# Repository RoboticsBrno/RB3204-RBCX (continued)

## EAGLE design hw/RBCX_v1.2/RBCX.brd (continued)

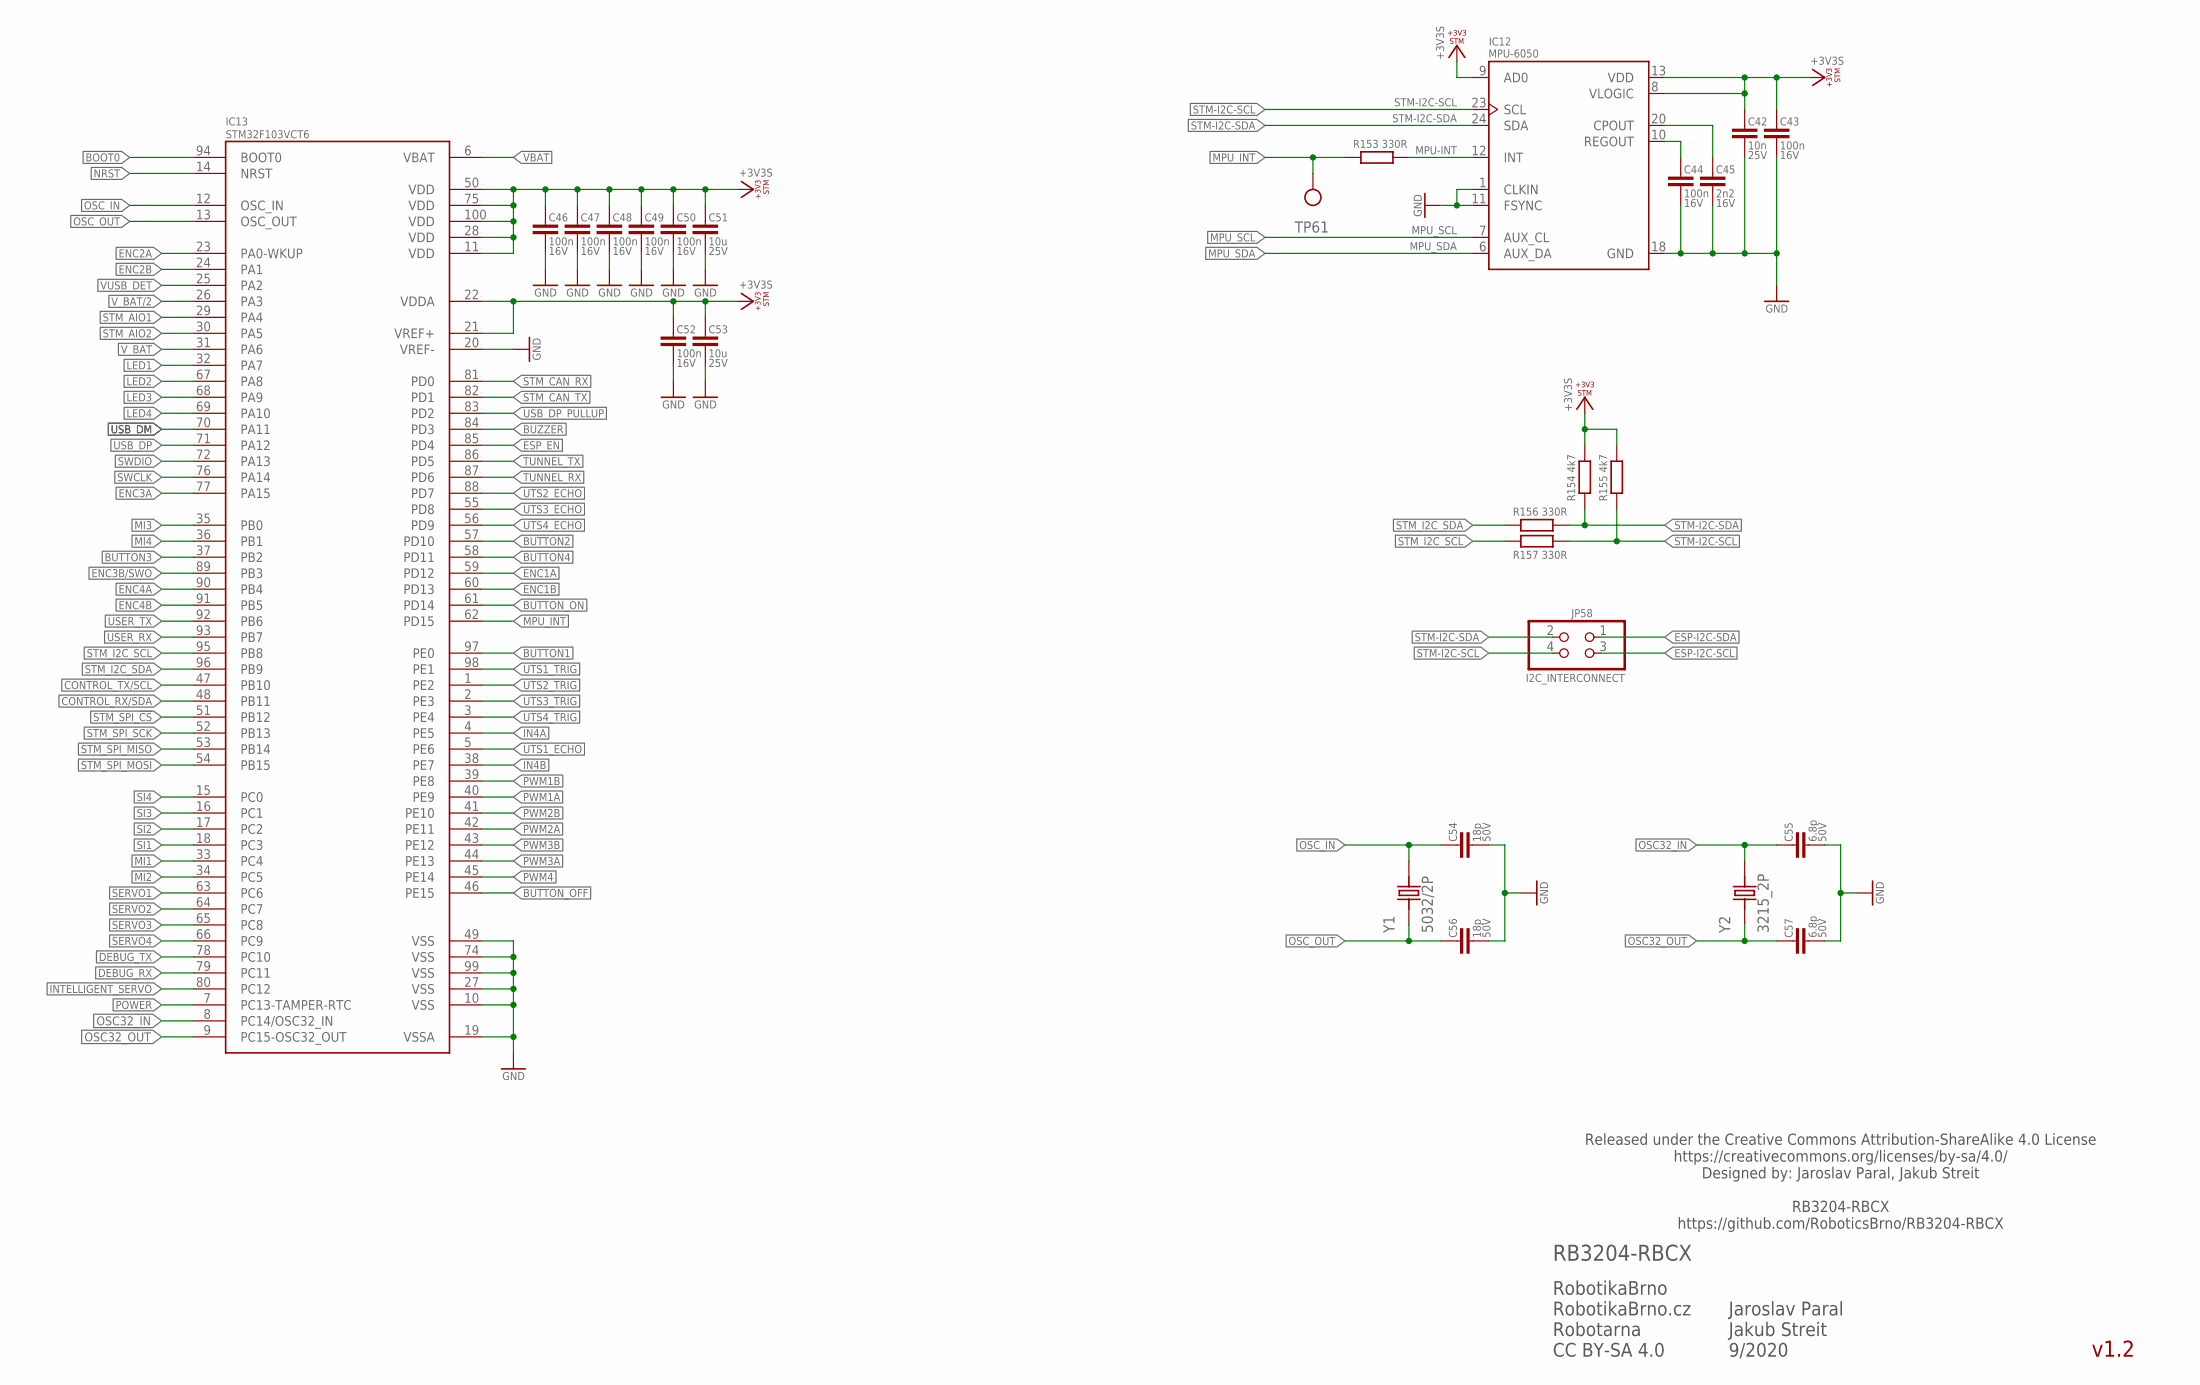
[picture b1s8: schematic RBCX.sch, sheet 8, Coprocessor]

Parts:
C42: 10n; C0402; VOLTAGE 25V
C43, C44, C46, C47, C48, C49, C50, C52: 100n; C0402; VOLTAGE 16V
C45: 2n2; C0402; VOLTAGE 16V
C51, C53: 10u; C0805; VOLTAGE 25V
C54, C56: 18p; C0402; VOLTAGE 50V
C55, C57: 6.8p; C0402; VOLTAGE 50V
IC12: MPU-6050; QFN50P400X400X95-24N
IC13: STM32F103VCT6; QFP50P1600X1600X160-100N_STM32F103VCT6
JP58: I2C_INTERCONNECT; 2X02
R153, R156, R157: 330R; R0402
R154, R155: 4k7; R0402
TP61: TP_06MM; TP_06
Y1: 5032/2P; OSCCC500X320X135
Y2: 3215_2P; SMD-3215_2P

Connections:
+3V3S: C42.1, C43.2, C46.2, C47.2, C48.2, C49.2, C50.2, C51.2, C52.2, C53.2, IC12.8 (VLOGIC), IC12.9 (AD0), IC12.13 (VDD), IC13.11 (VDD), IC13.21 (VREF+), IC13.22 (VDDA), IC13.28 (VDD), IC13.50 (VDD), IC13.75 (VDD), IC13.100 (VDD), R154.2, R155.2; also elsewhere on the board
BOOT0: IC13.94 (BOOT0); also elsewhere on the board
BUTTON1: IC13.97 (PE0); also elsewhere on the board
BUTTON2: IC13.57 (PD10); also elsewhere on the board
BUTTON3: IC13.37 (PB2); also elsewhere on the board
BUTTON4: IC13.58 (PD11); also elsewhere on the board
BUTTON_OFF: IC13.46 (PE15); also elsewhere on the board
BUTTON_ON: IC13.61 (PD14); also elsewhere on the board
BUZZER: IC13.84 (PD3); also elsewhere on the board
CONTROL_RX/SDA: IC13.48 (PB11); also elsewhere on the board
CONTROL_TX/SCL: IC13.47 (PB10); also elsewhere on the board
CPOUT: C45.2, IC12.20 (CPOUT)
DEBUG_RX: IC13.79 (PC11); also elsewhere on the board
DEBUG_TX: IC13.78 (PC10); also elsewhere on the board
ENC1A: IC13.59 (PD12); also elsewhere on the board
ENC1B: IC13.60 (PD13); also elsewhere on the board
ENC2A: IC13.23 (PA0-WKUP); also elsewhere on the board
ENC2B: IC13.24 (PA1); also elsewhere on the board
ENC3A: IC13.77 (PA15); also elsewhere on the board
ENC3B/SWO: IC13.89 (PB3); also elsewhere on the board
ENC4A: IC13.90 (PB4); also elsewhere on the board
ENC4B: IC13.91 (PB5); also elsewhere on the board
ESP-I2C-SCL: JP58.3; also elsewhere on the board
ESP-I2C-SDA: JP58.1; also elsewhere on the board
ESP_EN: IC13.85 (PD4); also elsewhere on the board
GND: C42.2, C43.1, C44.1, C45.1, C46.1, C47.1, C48.1, C49.1, C50.1, C51.1, C52.1, C53.1, C54.1, C55.1, C56.1, C57.1, IC12.1 (CLKIN), IC12.11 (FSYNC), IC12.18 (GND), IC13.10 (VSS), IC13.19 (VSSA), IC13.20 (VREF-), IC13.27 (VSS), IC13.49 (VSS), IC13.74 (VSS), IC13.99 (VSS); also elsewhere on the board
IN4A: IC13.4 (PE5); also elsewhere on the board
IN4B: IC13.38 (PE7); also elsewhere on the board
INTELLIGENT_SERVO: IC13.80 (PC12); also elsewhere on the board
LED1: IC13.32 (PA7); also elsewhere on the board
LED2: IC13.67 (PA8); also elsewhere on the board
LED3: IC13.68 (PA9); also elsewhere on the board
LED4: IC13.69 (PA10); also elsewhere on the board
MI1: IC13.33 (PC4); also elsewhere on the board
MI2: IC13.34 (PC5); also elsewhere on the board
MI3: IC13.35 (PB0); also elsewhere on the board
MI4: IC13.36 (PB1); also elsewhere on the board
MPU-INT: IC12.12 (INT), R153.2
MPU_INT: IC13.62 (PD15), R153.1, TP61.P$1
MPU_SCL: IC12.7 (AUX_CL); also elsewhere on the board
MPU_SDA: IC12.6 (AUX_DA); also elsewhere on the board
NRST: IC13.14 (NRST); also elsewhere on the board
OSC32_IN: C55.2, IC13.8 (PC14/OSC32_IN), Y2.2
OSC32_OUT: C57.2, IC13.9 (PC15-OSC32_OUT), Y2.1
OSC_IN: C54.2, IC13.12 (OSC_IN), Y1.2
OSC_OUT: C56.2, IC13.13 (OSC_OUT), Y1.1
POWER: IC13.7 (PC13-TAMPER-RTC); also elsewhere on the board
PWM1A: IC13.40 (PE9); also elsewhere on the board
PWM1B: IC13.39 (PE8); also elsewhere on the board
PWM2A: IC13.42 (PE11); also elsewhere on the board
PWM2B: IC13.41 (PE10); also elsewhere on the board
PWM3A: IC13.44 (PE13); also elsewhere on the board
PWM3B: IC13.43 (PE12); also elsewhere on the board
PWM4: IC13.45 (PE14); also elsewhere on the board
REGOUT: C44.2, IC12.10 (REGOUT)
SERVO1: IC13.63 (PC6); also elsewhere on the board
SERVO2: IC13.64 (PC7); also elsewhere on the board
SERVO3: IC13.65 (PC8); also elsewhere on the board
SERVO4: IC13.66 (PC9); also elsewhere on the board
SI1: IC13.18 (PC3); also elsewhere on the board
SI2: IC13.17 (PC2); also elsewhere on the board
SI3: IC13.16 (PC1); also elsewhere on the board
SI4: IC13.15 (PC0); also elsewhere on the board
STM-I2C-SCL: IC12.23 (SCL), JP58.4, R155.1, R157.2; also elsewhere on the board
STM-I2C-SDA: IC12.24 (SDA), JP58.2, R154.1, R156.2; also elsewhere on the board
STM_AIO1: IC13.29 (PA4); also elsewhere on the board
STM_AIO2: IC13.30 (PA5); also elsewhere on the board
STM_CAN_RX: IC13.81 (PD0); also elsewhere on the board
STM_CAN_TX: IC13.82 (PD1); also elsewhere on the board
STM_I2C_SCL: IC13.95 (PB8), R157.1
STM_I2C_SDA: IC13.96 (PB9), R156.1
STM_SPI_!CS: IC13.51 (PB12); also elsewhere on the board
STM_SPI_MISO: IC13.53 (PB14); also elsewhere on the board
STM_SPI_MOSI: IC13.54 (PB15); also elsewhere on the board
STM_SPI_SCK: IC13.52 (PB13); also elsewhere on the board
SWCLK: IC13.76 (PA14); also elsewhere on the board
SWDIO: IC13.72 (PA13); also elsewhere on the board
TUNNEL_RX: IC13.87 (PD6); also elsewhere on the board
TUNNEL_TX: IC13.86 (PD5); also elsewhere on the board
USB_DM: IC13.70 (PA11); also elsewhere on the board
USB_DP: IC13.71 (PA12); also elsewhere on the board
USB_DP_PULLUP: IC13.83 (PD2); also elsewhere on the board
USER_RX: IC13.93 (PB7); also elsewhere on the board
USER_TX: IC13.92 (PB6); also elsewhere on the board
UTS1_ECHO: IC13.5 (PE6); also elsewhere on the board
UTS1_TRIG: IC13.98 (PE1); also elsewhere on the board
UTS2_ECHO: IC13.88 (PD7); also elsewhere on the board
UTS2_TRIG: IC13.1 (PE2); also elsewhere on the board
UTS3_ECHO: IC13.55 (PD8); also elsewhere on the board
UTS3_TRIG: IC13.2 (PE3); also elsewhere on the board
UTS4_ECHO: IC13.56 (PD9); also elsewhere on the board
UTS4_TRIG: IC13.3 (PE4); also elsewhere on the board
VBAT: IC13.6 (VBAT); also elsewhere on the board
VUSB_DET: IC13.25 (PA2); also elsewhere on the board
V_BAT: IC13.31 (PA6); also elsewhere on the board
V_BAT/2: IC13.26 (PA3); also elsewhere on the board

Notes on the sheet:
v1.2
RobotikaBrno RobotikaBrno.cz Robotarna CC BY-SA 4.0
RB3204-RBCX
Released under the Creative Commons Attribution-ShareAlike 4.0 License https://creativecommons.org/licenses/by-sa/4.0/ Designed by: Jaroslav Paral, Jakub Streit RB3204-RBCX https://github.com/RoboticsBrno/RB3204-RBCX
Jaroslav Paral Jakub Streit 9/2020

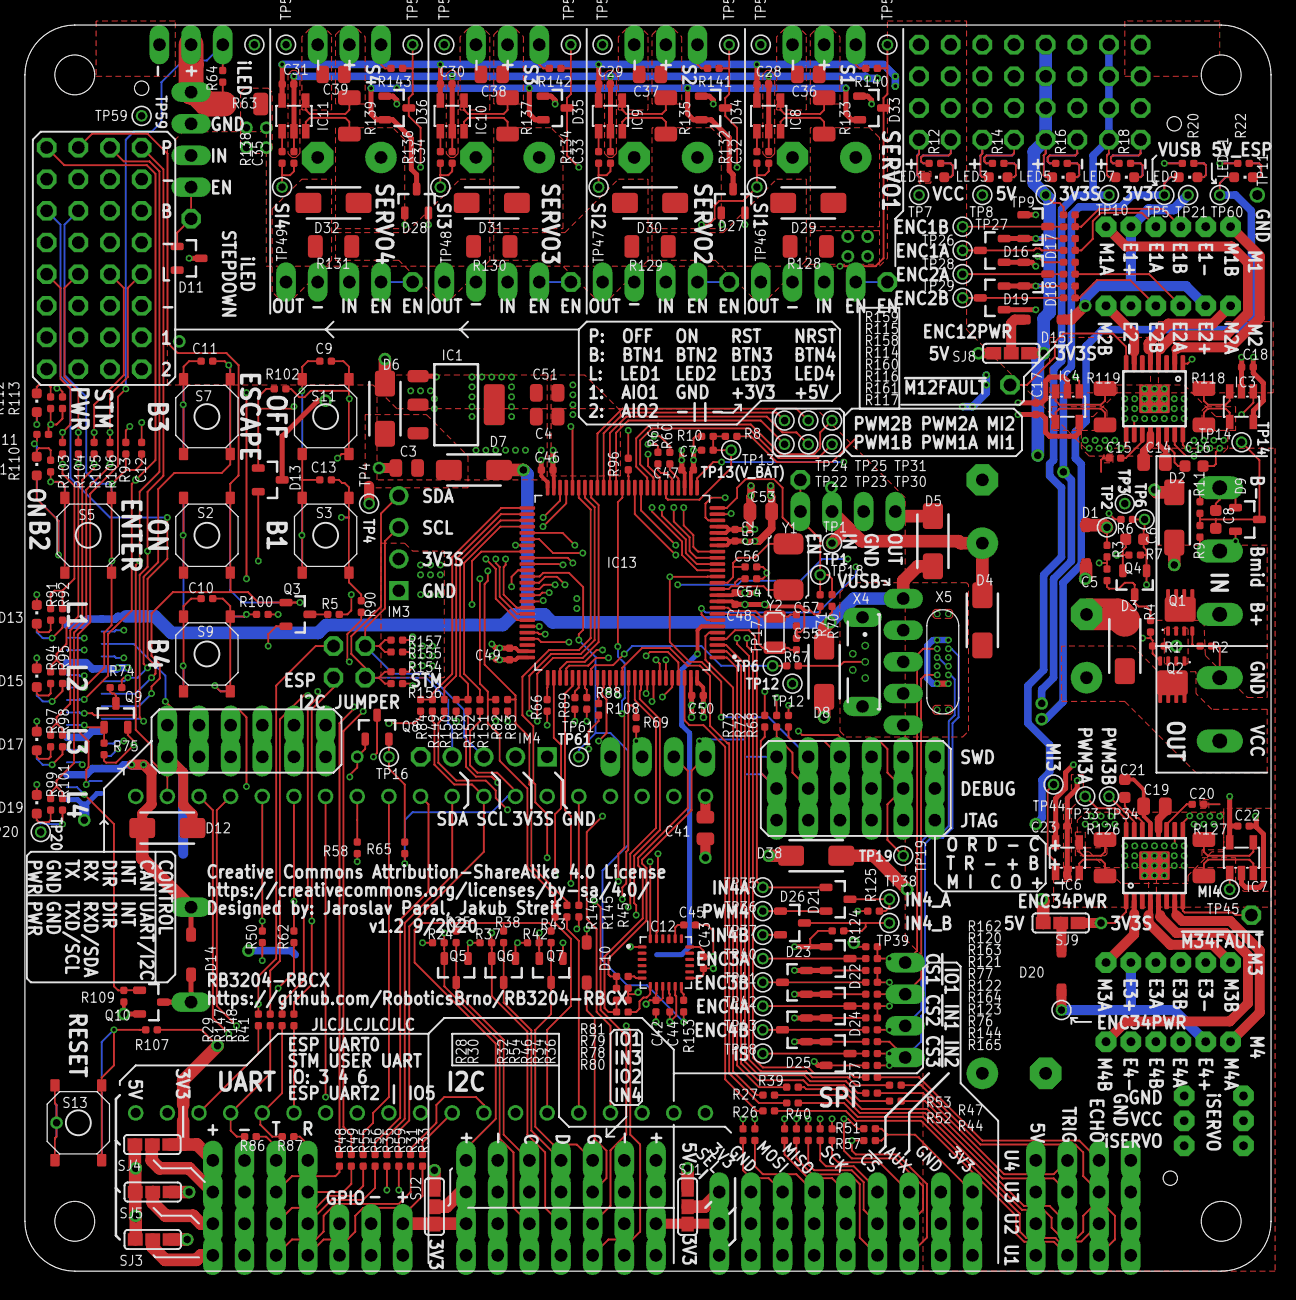
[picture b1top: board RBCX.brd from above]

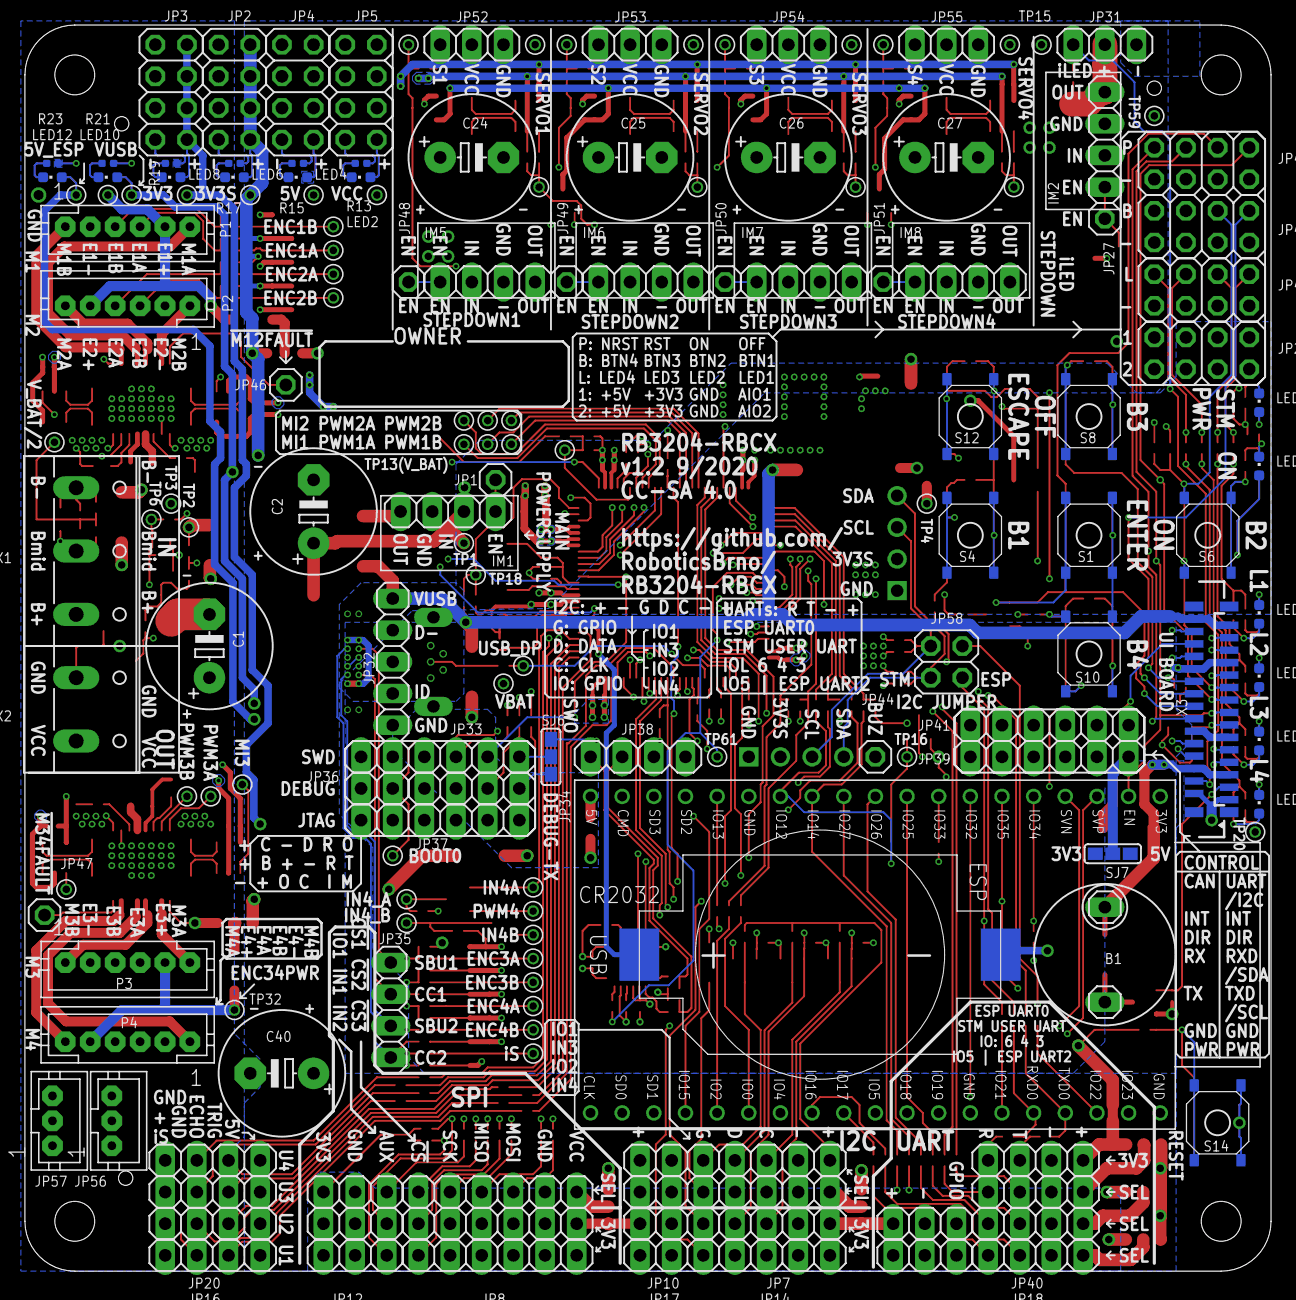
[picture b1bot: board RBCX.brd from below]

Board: 4 copper layers, 100.0 x 100.0 mm, 471 parts (110 on the bottom side), 294 nets.

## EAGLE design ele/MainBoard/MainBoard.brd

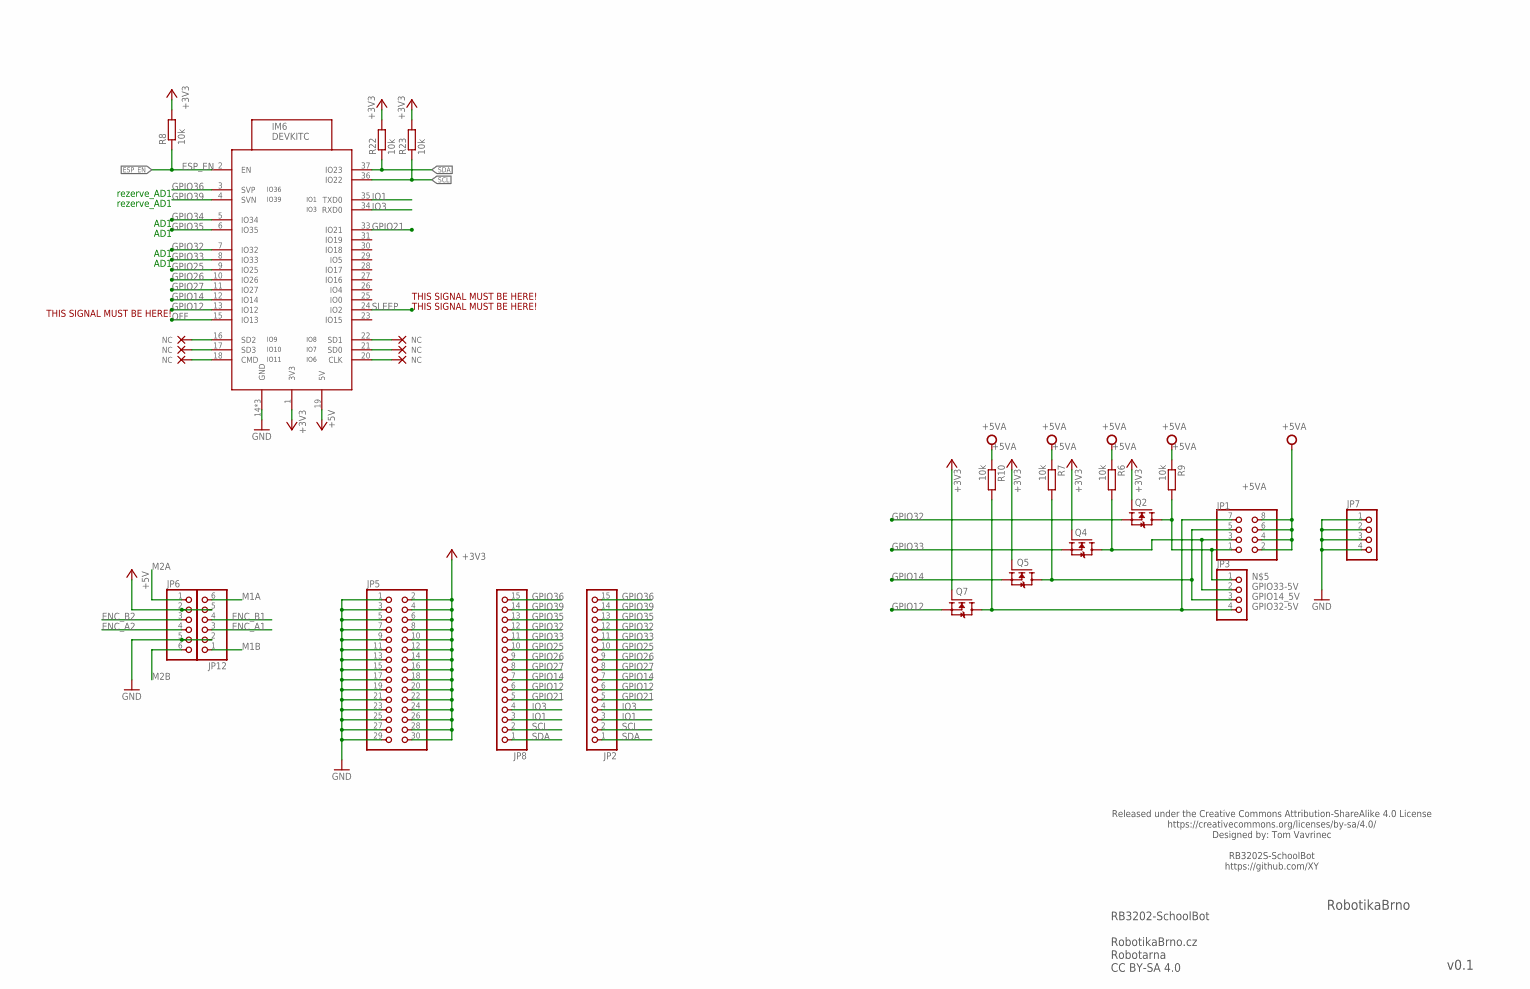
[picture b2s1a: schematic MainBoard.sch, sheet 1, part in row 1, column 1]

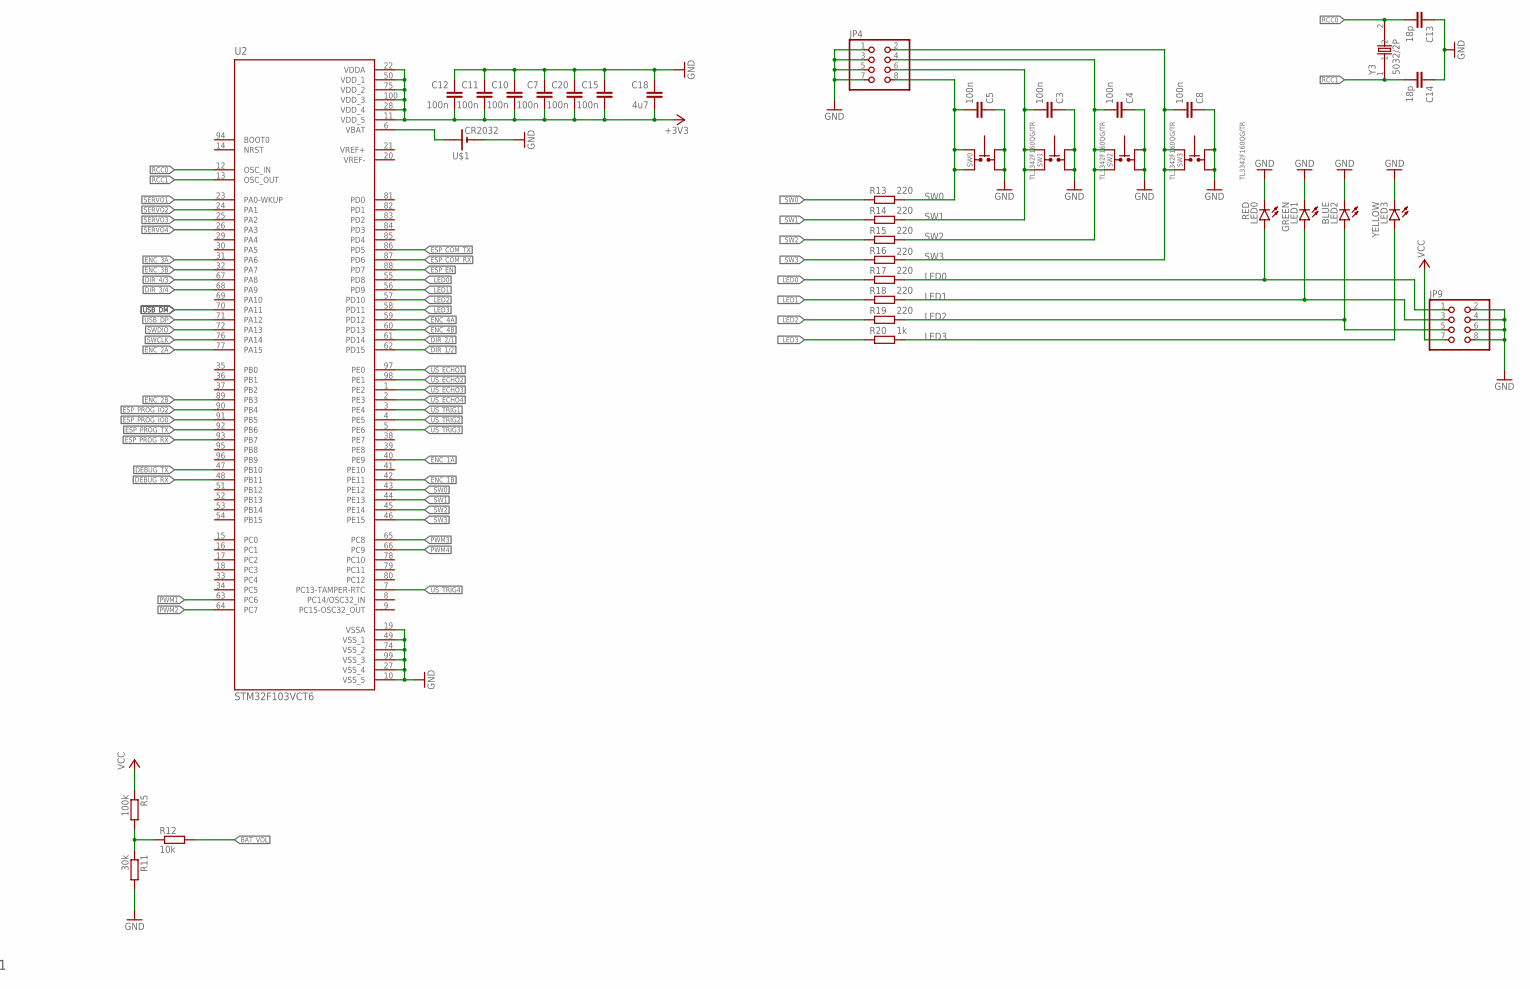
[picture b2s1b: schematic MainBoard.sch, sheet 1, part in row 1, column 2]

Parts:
C3, C4, C5, C8: 100n; C0402
C7, C10, C11, C12, C15, C20: 100n; C0402; LCSC_ID C1525
C13, C14: 18p; C0402; LCSC_ID C1549
C18: 4u7; C0603; LCSC_ID C19666
IM6: DEVKITC
JP1, JP4, JP9: PINHD-2X4; 2X04
JP2, JP8: PINHD-1X15; 1X15
JP3, JP7: PINHD-1X4; 1X04
JP5: PINHD-2X15; 2X15
JP6, JP12: PINHD-1X6; 1X06
LED0: RED; SML0603
LED1: GREEN; SML0603
LED2: BLUE; SML0603
LED3: YELLOW; SML0603
Q2, Q4, Q5, Q7: N-MOSFET-SOT23-GSD; SOT23
R5: 100k; R0402
R6, R7, R8, R9, R10, R12, R22, R23: 10k; R0402
R11: 30k; R0402
R13, R14, R15, R16, R17, R18, R19: 220; R0402
R20: 1k; R0402
SW0, SW1, SW2, SW3: TL3342F160QG/TR
U2: STM32F103VCT6; QFP50P1600X1600X160-100N_STM32F103VCT6
U$1: CR2032; CH075
Y3: 5032/2P; OSCCC500X320X135

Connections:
3,3!KNOFLIK: U2.6 (VBAT), U$1.+
+3V3: C7.2, C10.2, C11.2, C12.2, C15.2, C18.2, C20.2, IM6.1 (3V3), JP5.2, JP5.4, JP5.6, JP5.8, JP5.10, JP5.12, JP5.14, JP5.16, JP5.18, JP5.20, JP5.22, JP5.24, JP5.26, JP5.28, JP5.30, Q2.1 (G), Q4.1 (G), Q5.1 (G), Q7.1 (G), R8.2, R22.2, R23.2, U2.11 (VDD_5), U2.22 (VDDA), U2.28 (VDD_4), U2.50 (VDD_1), U2.75 (VDD_2), U2.100 (VDD_3); also elsewhere on the board
+5V: IM6.19 (5V), JP6.2, JP12.5; also elsewhere on the board
+5VA: JP1.2, JP1.4, JP1.6, JP1.8, R6.1, R7.1, R9.1, R10.1
BAT_VOL: R12.2
DEBUG_RX: U2.48 (PB11)
DEBUG_TX: U2.47 (PB10)
DIR_1/2: U2.62 (PD15)
DIR_2/1: U2.61 (PD14)
DIR_3/4: U2.68 (PA9)
DIR_4/3: U2.67 (PA8)
ENC_1A: U2.40 (PE9)
ENC_1B: U2.42 (PE11)
ENC_2A: U2.77 (PA15)
ENC_2B: U2.89 (PB3)
ENC_3A: U2.31 (PA6)
ENC_3B: U2.32 (PA7)
ENC_4A: U2.59 (PD12)
ENC_4B: U2.60 (PD13)
ENC_A1: JP12.3
ENC_A2: JP6.4
ENC_B1: JP12.4
ENC_B2: JP6.3
ESP_COM_RX: U2.87 (PD6)
ESP_COM_TX: U2.86 (PD5)
ESP_EN: IM6.2 (EN), R8.1, U2.88 (PD7)
ESP_PROG_IO0: U2.91 (PB5)
ESP_PROG_IO2: U2.90 (PB4)
ESP_PROG_RX: U2.93 (PB7)
ESP_PROG_TX: U2.92 (PB6)
GND: C3.1, C4.1, C5.1, C7.1, C8.1, C10.1, C11.1, C12.1, C13.1, C14.1, C15.1, C18.1, C20.1, IM6.14 (GND), IM6.32 (GND), IM6.38 (GND), JP4.1, JP4.3, JP4.5, JP4.7, JP5.1, JP5.3, JP5.5, JP5.7, JP5.9, JP5.11, JP5.13, JP5.15, JP5.17, JP5.19, JP5.21, JP5.23, JP5.25, JP5.27, JP5.29, JP6.5, JP7.1, JP7.2, JP7.3, JP7.4, JP9.2, JP9.4, JP9.6, JP9.8, JP12.2, LED0.C, LED1.C, LED2.C, LED3.C, R11.2, SW0.1, SW0.2, SW1.1, SW1.2, SW2.1, SW2.2, SW3.1, SW3.2, U2.10 (VSS_5), U2.19 (VSSA), U2.27 (VSS_4), U2.49 (VSS_1), U2.74 (VSS_2), U2.99 (VSS_3), U$1.-; also elsewhere on the board
GPIO12: IM6.13 (IO12), JP2.6, JP8.6, Q7.2 (S)
GPIO14: IM6.12 (IO14), JP2.7, JP8.7, Q5.2 (S)
GPIO14_5V: JP1.5, JP3.3, Q5.3 (D), R7.2
GPIO21: IM6.33 (IO21), JP2.5, JP8.5
GPIO25: IM6.9 (IO25), JP2.10, JP8.10
GPIO26: IM6.10 (IO26), JP2.9, JP8.9
GPIO27: IM6.11 (IO27), JP2.8, JP8.8
GPIO32: IM6.7 (IO32), JP2.12, JP8.12, Q2.2 (S)
GPIO32-5V: JP1.7, JP3.4, Q7.3 (D), R10.2
GPIO33: IM6.8 (IO33), JP2.11, JP8.11, Q4.2 (S)
GPIO33-5V: JP1.3, JP3.2, Q4.3 (D), R6.2
GPIO34: IM6.5 (IO34)
GPIO35: IM6.6 (IO35), JP2.13, JP8.13; also elsewhere on the board
GPIO36: IM6.3 (SVP), JP2.15, JP8.15
GPIO39: IM6.4 (SVN), JP2.14, JP8.14
IO1: IM6.35 (TXD0), JP2.3, JP8.3
IO3: IM6.34 (RXD0), JP2.4, JP8.4
IO9_NC: IM6.16 (SD2)
IO9_NC1: IM6.20 (CLK)
IO10_NC: IM6.17 (SD3)
IO10_NC1: IM6.21 (SD0)
IO11_NC: IM6.18 (CMD)
IO11_NC1: IM6.22 (SD1)
LED0: JP9.1, LED0.A, R17.2
LED1: JP9.3, LED1.A, R18.2
LED2: JP9.5, LED2.A, R19.2
LED3: LED3.A, R20.2
M1A: JP12.6; also elsewhere on the board
M1B: JP12.1; also elsewhere on the board
M2A: JP6.1; also elsewhere on the board
M2B: JP6.6; also elsewhere on the board
unnamed: R5.2, R11.1, R12.1
unnamed: JP1.1, JP3.1, Q2.3 (D), R9.2
OFF: IM6.15 (IO13); also elsewhere on the board
PWM1: U2.63 (PC6)
PWM2: U2.64 (PC7)
PWM3: U2.65 (PC8)
PWM4: U2.66 (PC9)
RCC0: C13.2, U2.12 (OSC_IN), Y3.2
RCC1: C14.2, U2.13 (OSC_OUT), Y3.1
SCL: IM6.36 (IO22), JP2.2, JP8.2, R23.1
SDA: IM6.37 (IO23), JP2.1, JP8.1, R22.1
SERVO1: U2.23 (PA0-WKUP)
SERVO2: U2.24 (PA1)
SERVO3: U2.25 (PA2)
SERVO4: U2.26 (PA3)
SLEEP: IM6.24 (IO2); also elsewhere on the board
SW0: C5.2, JP4.8, R13.2, SW0.3, SW0.4
SW1: C3.2, JP4.6, R14.2, SW1.3, SW1.4
SW2: C4.2, JP4.4, R15.2, SW2.3, SW2.4
SW3: C8.2, JP4.2, R16.2, SW3.3, SW3.4
SWCLK: U2.76 (PA14)
SWDIO: U2.72 (PA13)
USB_DM: U2.70 (PA11)
USB_DP: U2.71 (PA12)
US_ECHO1: U2.97 (PE0)
US_ECHO2: U2.98 (PE1)
US_ECHO3: U2.1 (PE2)
US_ECHO4: U2.2 (PE3)
US_TRIG1: U2.3 (PE4)
US_TRIG2: U2.4 (PE5)
US_TRIG3: U2.5 (PE6)
US_TRIG4: U2.7 (PC13-TAMPER-RTC)
VCC: JP9.7, R5.1; also elsewhere on the board
VREF+: U2.21 (VREF+)
VREF-: U2.20 (VREF-)
_LED0: R17.1, U2.55 (PD8)
_LED1: R18.1, U2.56 (PD9)
_LED2: R19.1, U2.57 (PD10)
_LED3: R20.1, U2.58 (PD11)
_SW0: R13.1, U2.43 (PE12)
_SW1: R14.1, U2.44 (PE13)
_SW2: R15.1, U2.45 (PE14)
_SW3: R16.1, U2.46 (PE15)

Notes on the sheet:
AD1
rezerve_AD1
RB3202-SchoolBot RobotikaBrno.cz Robotarna CC BY-SA 4.0
RobotikaBrno
v0.1
Released under the Creative Commons Attribution-ShareAlike 4.0 License https://creativecommons.org/licenses/by-sa/4.0/ Designed by: Tom Vavrinec RB3202S-SchoolBot https://github.com/XY
THIS SIGNAL MUST BE HERE!

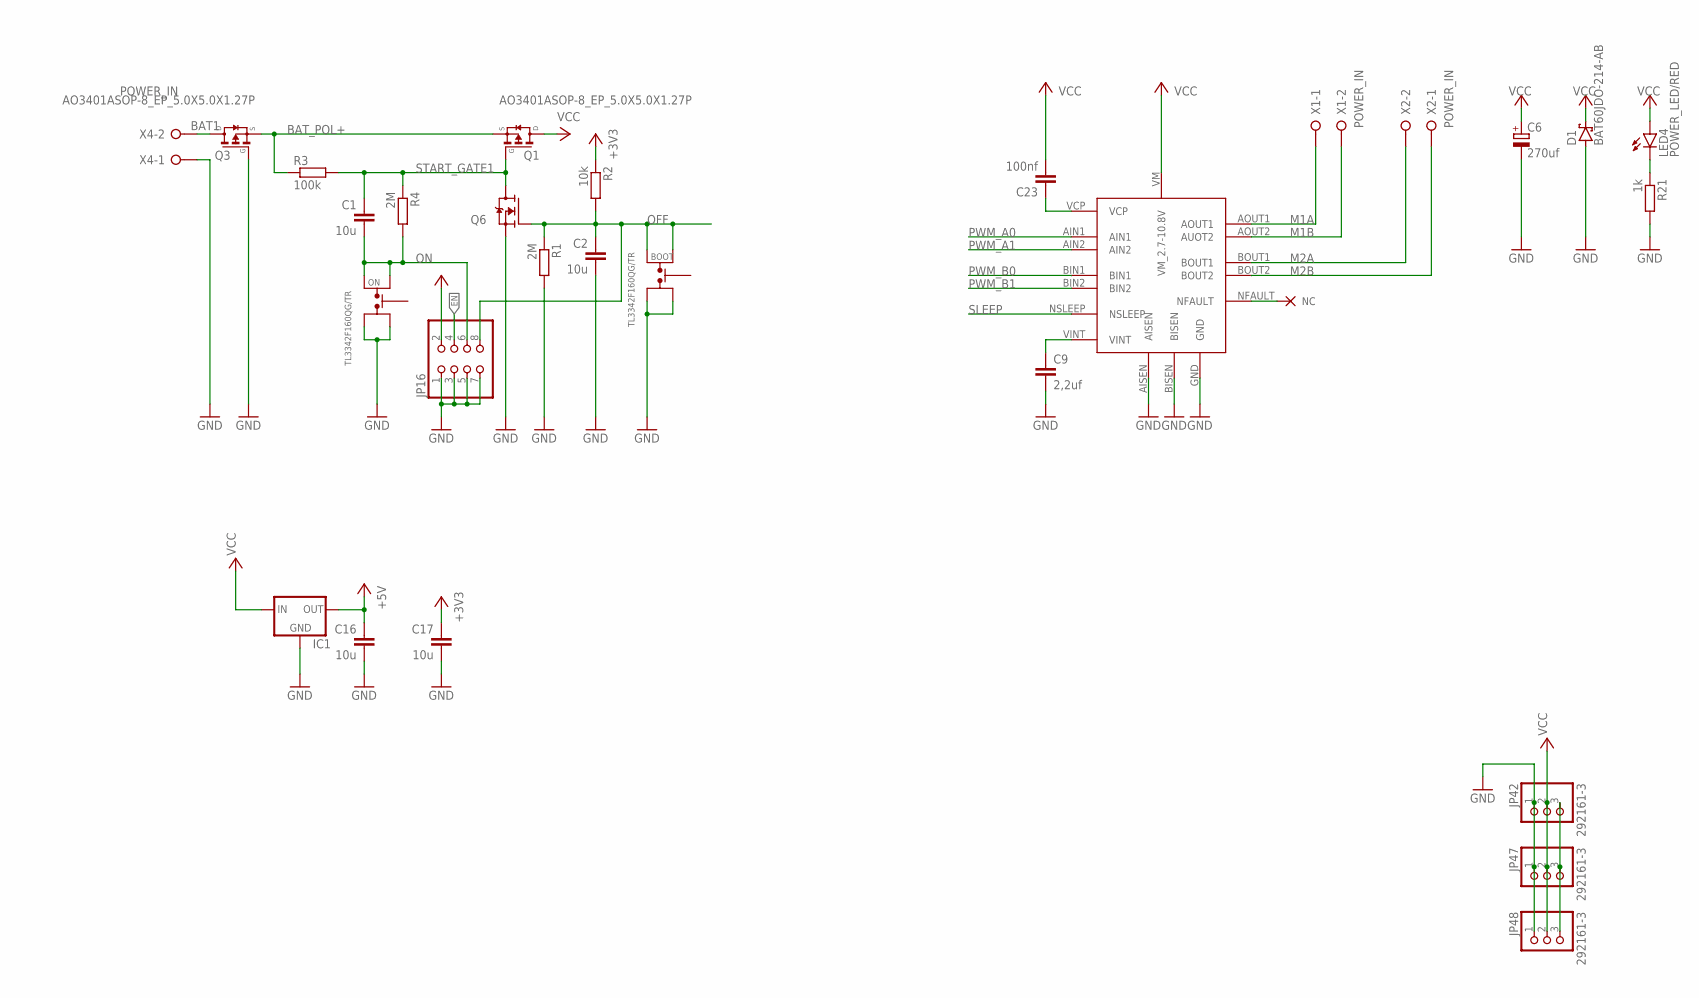
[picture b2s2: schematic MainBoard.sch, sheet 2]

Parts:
BOOT: TL3342F160QG/TR
C1, C2, C16, C17: 10u; C1206
C6: 270uf; 140CLH-1010
C9: 2,2uf; C0805
C23: 100nf; C0402
D1: BAT60JDO-214-AB; DO214BA
IC1: LM1117; SOT223
JP16: PINHD-2X4; 2X04
JP42, JP47, JP48: 292161-3
LED4: POWER_LED/RED; SML0603
ON: TL3342F160QG/TR
Q1, Q3: AO3401ASOP-8_EP_5.0X5.0X1.27P; SOP-8_EP_5.0X5.0X1.27P
Q6: N-MOSFET-SOT23-GSD; SOT23
R1, R4: 2M; R0402
R2: 10k; R0402
R3: 100k; R0402
R21: 1k; R0402
U$9: DRV8833HTSSOP; HTSSOP
X1, X2, X4: POWER_IN; W237-132

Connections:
+3V3: C17.1, R2.1; also elsewhere on the board
+5V: C16.1, IC1.2 (OUT), IC1.4 (OUT), JP16.2; also elsewhere on the board
BAT1: Q3.5 (D), Q3.6 (D), Q3.7 (D), Q3.8 (D), Q3.9 (D), X4.2
BAT_POL+: Q1.1 (S), Q1.2 (S), Q1.3 (S), Q3.1 (S), Q3.2 (S), Q3.3 (S), R3.1
EN: JP16.4
GND: BOOT.1, BOOT.2, C2.2, C6.-, C9.2, C16.2, C17.2, D1.A, IC1.1 (GND), JP16.1, JP16.3, JP16.5, JP16.7, JP42.1, JP47.1, JP48.1, ON.1, ON.2, Q3.4 (G), Q6.2 (S), R1.2, R21.2, U$9.AISEN, U$9.BISEN, U$9.GND, X4.1; also elsewhere on the board
GPIO35: JP42.3, JP47.3, JP48.3; also elsewhere on the board
IO9_NC2: U$9.NFAULT
M1A: U$9.AOUT1, X1.1; also elsewhere on the board
M1B: U$9.AOUT2 (AUOT2), X1.2; also elsewhere on the board
M2A: U$9.BOUT1, X2.2; also elsewhere on the board
M2B: U$9.BOUT2, X2.1; also elsewhere on the board
unnamed: LED4.C, R21.1
unnamed: C9.1, U$9.VINT
unnamed: C23.1, U$9.VCP
OFF: BOOT.3, BOOT.4, C2.1, JP16.8, Q6.1 (G), R1.1, R2.2; also elsewhere on the board
ON: C1.2, JP16.6, ON.3, ON.4, R4.2
PWM_A0: U$9.AIN1
PWM_A1: U$9.AIN2
PWM_B0: U$9.BIN1
PWM_B1: U$9.BIN2
SLEEP: U$9.NSLEEP; also elsewhere on the board
START_GATE1: C1.1, Q1.4 (G), Q6.3 (D), R3.2, R4.1
VCC: C6.+, C23.2, D1.C, IC1.3 (IN), JP42.2, JP47.2, JP48.2, LED4.A, Q1.5 (D), Q1.6 (D), Q1.7 (D), Q1.8 (D), Q1.9 (D), U$9.VM (VM_2.7-10.8V); also elsewhere on the board

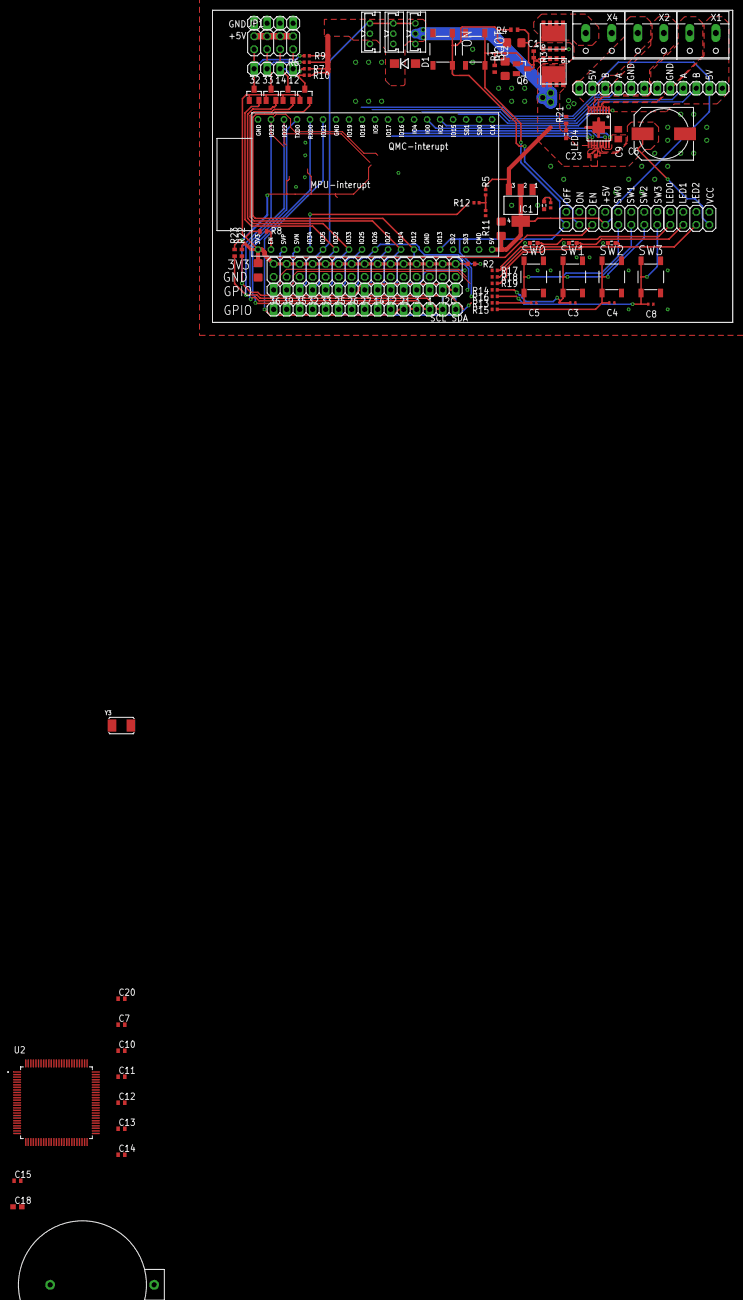
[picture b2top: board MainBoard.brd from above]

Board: 2 copper layers, 101.6 x 61.0 mm, 85 parts (0 on the bottom side), 58 nets.

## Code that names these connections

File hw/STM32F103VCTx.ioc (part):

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Mcu.Name=STM32F103V(C-D-E)Tx
Mcu.Package=LQFP100
Mcu.UserName=STM32F103VCTx
PA0-WKUP.GPIOParameters=GPIO_Label
PA0-WKUP.GPIO_Label=SERVO1 (TIM5_CH1)
PA0-WKUP.Signal=S_TIM5_CH1
PA1.GPIOParameters=GPIO_Label
PA1.GPIO_Label=SERVO2 (TIM5_CH2)
PA1.Signal=S_TIM5_CH2
PA10.GPIOParameters=GPIO_Label
PA10.GPIO_Label=DEBUG (USART1_RX)
PA10.Mode=Asynchronous
PA10.Signal=USART1_RX
PA11.Mode=Device
PA11.Signal=USB_DM
PA12.Mode=Device
PA12.Signal=USB_DP
PA13.Signal=SYS_JTMS-SWDIO
PA14.Signal=SYS_JTCK-SWCLK
PA15.GPIOParameters=GPIO_Label
PA15.GPIO_Label=ENC1A (TIM2_CH1)
PA15.Signal=S_TIM2_CH1_ETR
PA2.GPIOParameters=GPIO_Label
PA2.GPIO_Label=SERVO3 (TIM5_CH3)
PA2.Signal=S_TIM5_CH3
PA3.GPIOParameters=GPIO_Label
PA3.GPIO_Label=SERVO4 (TIM5_CH4)
PA3.Signal=S_TIM5_CH4
PA4.GPIOParameters=GPIO_Label
PA4.GPIO_Label=AIO (DAC_OUT1/ADC2_IN4)
PA4.Signal=COMP_DAC1_group
PA5.GPIOParameters=GPIO_Label
PA5.GPIO_Label=AIO (DAC_OUT1/ADC2_IN5)
PA5.Signal=COMP_DAC2_group
PA6.GPIOParameters=GPIO_Label
PA6.GPIO_Label=VBAT (ADC2_IN6)
PA6.Signal=ADCx_IN6
PA7.GPIOParameters=GPIO_Label
PA7.GPIO_Label=VBAT/2 (ADC2_IN7)
PA7.Signal=ADCx_IN7
PA8.GPIOParameters=GPIO_Label
PA8.GPIO_Label=USB_DP_PULLUP
PA8.Signal=GPIO_Output
PA9.GPIOParameters=GPIO_Label
PA9.GPIO_Label=DEBUG (USART1_TX)
PA9.Mode=Asynchronous
PA9.Signal=USART1_TX
PB0.GPIOParameters=GPIO_Label
PB0.GPIO_Label=MI3 (ADC1_IN8)
PB0.Signal=ADCx_IN8
PB1.GPIOParameters=GPIO_Label
PB1.GPIO_Label=MI4 (ADC1_IN9)
PB1.Signal=ADCx_IN9
PB10.GPIOParameters=GPIO_Label
PB10.GPIO_Label=I2C_SCL
PB10.Signal=I2C2_SCL
PB11.GPIOParameters=GPIO_Label
PB11.GPIO_Label=I2C_SDA
PB11.Signal=I2C2_SDA
PB12.GPIOParameters=GPIO_Label
PB12.GPIO_Label=SPI_NSS/ESP_JTAG_TMS
PB12.Mode=NSS_Signal_Hard_Output
PB12.Signal=SPI2_NSS
PB13.GPIOParameters=GPIO_Label
PB13.GPIO_Label=SPI_SCK/ESP_JTAG_TCK
PB13.Mode=Full_Duplex_Master
PB13.Signal=SPI2_SCK
PB14.GPIOParameters=GPIO_Label
PB14.GPIO_Label=SPI_MISO/ESP_JTAG_TDO
PB14.Mode=Full_Duplex_Master
PB14.Signal=SPI2_MISO
PB15.GPIOParameters=GPIO_Label
PB15.GPIO_Label=SPI_MOSI/ESP_JTAG_TDI
PB15.Mode=Full_Duplex_Master
PB15.Signal=SPI2_MOSI
PB2.GPIOParameters=GPIO_PuPd,GPIO_Label
PB2.GPIO_Label=BUTTON3
PB2.GPIO_PuPd=GPIO_PULLUP
PB2.Signal=GPIO_Input
PB3.GPIOParameters=GPIO_Label
PB3.GPIO_Label=ENC1B (TIM2_CH2)
PB3.Signal=S_TIM2_CH2
PB4.GPIOParameters=GPIO_Label
PB4.GPIO_Label=ENC2A (TIM3_CH1)
PB4.Signal=S_TIM3_CH1
PB5.GPIOParameters=GPIO_Label
PB5.GPIO_Label=ENC2B (TIM3_CH2)
PB5.Signal=S_TIM3_CH2
PB6.GPIOParameters=GPIO_Label
PB6.GPIO_Label=BUTTON1
PB6.Signal=GPIO_Input
PB7.GPIOParameters=GPIO_Label
PB7.GPIO_Label=MPU_INT
PB7.Signal=GPIO_Input
PB8.GPIOParameters=GPIO_Label
PB8.GPIO_Label=CAN1_RX/I2C1_SCL
PB8.Signal=CAN_RX
PB9.GPIOParameters=GPIO_Label
PB9.GPIO_Label=CAN1_TX/I2C1_SDA
PB9.Signal=CAN_TX
PC0.GPIOParameters=GPIO_Label
PC0.GPIO_Label=SI1 (ADC3_IN10)
PC0.Signal=ADCx_IN10
PC1.GPIOParameters=GPIO_Label
PC1.GPIO_Label=SI2 (ADC3_IN11)
PC1.Signal=ADCx_IN11
PC10.GPIOParameters=GPIO_Label
PC10.GPIO_Label=ESP_COM (UART4_TX)
PC10.Mode=Asynchronous
PC10.Signal=UART4_TX
PC11.GPIOParameters=GPIO_Label
PC11.GPIO_Label=ESP_COM (UART4_RX)
PC11.Mode=Asynchronous
PC11.Signal=UART4_RX
PC12.GPIOParameters=GPIO_Label
PC12.GPIO_Label=ESP_PROG (UART5_TX)
PC12.Mode=Asynchronous
PC12.Signal=UART5_TX
PC13-TAMPER-RTC.GPIOParameters=GPIO_PuPd,GPIO_Label
PC13-TAMPER-RTC.GPIO_Label=VUSB_DET
PC13-TAMPER-RTC.GPIO_PuPd=GPIO_PULLUP
PC13-TAMPER-RTC.Signal=GPIO_Input
PC14-OSC32_IN.Mode=LSE-External-Oscillator
PC14-OSC32_IN.Signal=RCC_OSC32_IN
PC15-OSC32_OUT.Mode=LSE-External-Oscillator
PC15-OSC32_OUT.Signal=RCC_OSC32_OUT
PC2.GPIOParameters=GPIO_Label
PC2.GPIO_Label=SI3 (ADC3_IN12)
PC2.Signal=ADCx_IN12
PC3.GPIOParameters=GPIO_Label
PC3.GPIO_Label=SI4 (ADC3_IN13)
PC3.Signal=ADCx_IN13
PC4.GPIOParameters=GPIO_Label
PC4.GPIO_Label=MI1 (ADC1_IN14)
PC4.Signal=ADCx_IN14
PC5.GPIOParameters=GPIO_Label
PC5.GPIO_Label=MI2 (ADC1_IN15)
PC5.Signal=ADCx_IN15
PC6.GPIOParameters=GPIO_Label
PC6.GPIO_Label=ENC4A (TIM8_CH1)
PC6.Signal=S_TIM8_CH1
PC7.GPIOParameters=GPIO_Label
PC7.GPIO_Label=ENC4B (TIM8_CH2)
PC7.Signal=S_TIM8_CH2
PC8.GPIOParameters=GPIO_Label
PC8.GPIO_Label=ESP_EN
PC8.Signal=GPIO_Output
PC9.GPIOParameters=GPIO_Label
PC9.GPIO_Label=BUTTON_ON
PC9.Signal=GPIO_Output
PD0.GPIOParameters=GPIO_Label
PD0.GPIO_Label=IN4B
PD0.Signal=GPIO_Output
PD1.GPIOParameters=GPIO_Label
PD1.GPIO_Label=IN4A
PD1.Signal=GPIO_Output
PD10.GPIOParameters=GPIO_Label
PD10.GPIO_Label=LED1
PD10.Signal=GPIO_Output
PD11.GPIOParameters=GPIO_Label
PD11.GPIO_Label=LED2
PD11.Signal=GPIO_Output
PD12.GPIOParameters=GPIO_Label
PD12.GPIO_Label=ENC3A (TIM4_CH1)
PD12.Signal=S_TIM4_CH1
PD13.GPIOParameters=GPIO_Label
PD13.GPIO_Label=ENC3B (TIM4_CH2)
PD13.Signal=S_TIM4_CH2
PD14.GPIOParameters=GPIO_PuPd,GPIO_Label,GPIO_ModeDefaultOutputPP
PD14.GPIO_Label=LED3
PD14.GPIO_ModeDefaultOutputPP=GPIO_MODE_OUTPUT_OD
PD14.GPIO_PuPd=GPIO_NOPULL
PD14.Signal=GPIO_Output
PD15.GPIOParameters=GPIO_Label,GPIO_ModeDefaultOutputPP
PD15.GPIO_Label=LED4
PD15.GPIO_ModeDefaultOutputPP=GPIO_MODE_OUTPUT_OD
PD15.Signal=GPIO_Output
PD2.GPIOParameters=GPIO_Label
PD2.GPIO_Label=ESP_PROG (UART5_RX)
PD2.Mode=Asynchronous
PD2.Signal=UART5_RX
PD3.GPIOParameters=GPIO_Label
PD3.GPIO_Label=BUTTON2
PD3.Signal=GPIO_Input
PD4.GPIOParameters=GPIO_Label
PD4.GPIO_Label=BUTTON3
PD4.Signal=GPIO_Input
PD5.Mode=Asynchronous
PD5.Signal=USART2_TX
PD6.Mode=Asynchronous
PD6.Signal=USART2_RX
PD7.GPIOParameters=GPIO_Label
PD7.GPIO_Label=BUZZER
PD7.Signal=GPIO_Output
PD8.GPIOParameters=GPIO_Label
PD8.GPIO_Label=INTELLIGENT_SERVO
PD8.Signal=USART3_TX
PD9.GPIOParameters=GPIO_Label
PD9.GPIO_Label=POWER
PD9.Signal=GPIO_Output
PE0.GPIOParameters=GPIO_Label
PE0.GPIO_Label=UTS1_TRIG
PE0.Signal=GPIO_Output
PE1.GPIOParameters=GPIO_PuPd,GPIO_Label,GPIO_ModeDefaultEXTI
PE1.GPIO_Label=UTS1_ECHO
PE1.GPIO_ModeDefaultEXTI=GPIO_MODE_IT_RISING_FALLING
PE1.GPIO_PuPd=GPIO_PULLUP
PE1.Signal=GPXTI1
PE10.GPIOParameters=GPIO_Label
PE10.GPIO_Label=PWM2B (TIM1_CH2N)
PE10.Mode=PWM Generation2 CH2 CH2N
PE10.Signal=TIM1_CH2N
PE11.GPIOParameters=GPIO_Label
PE11.GPIO_Label=PWM2A (TIM1_CH2)
PE11.Signal=S_TIM1_CH2
PE12.GPIOParameters=GPIO_Label
PE12.GPIO_Label=PWM3B (TIM1_CH3N)
PE12.Mode=PWM Generation3 CH3 CH3N
PE12.Signal=TIM1_CH3N
PE13.GPIOParameters=GPIO_Label
PE13.GPIO_Label=PWM3A (TIM1_CH3)
PE13.Signal=S_TIM1_CH3
PE14.GPIOParameters=GPIO_Label
PE14.GPIO_Label=PWM4 (TIM1_CH4)
PE14.Signal=S_TIM1_CH4
PE15.GPIOParameters=GPIO_PuPd,GPIO_Label
PE15.GPIO_Label=BUTTON_OFF
PE15.GPIO_PuPd=GPIO_PULLUP
PE15.Signal=GPIO_Input
PE2.GPIOParameters=GPIO_Label
PE2.GPIO_Label=UTS2_TRIG
PE2.Signal=GPIO_Output
PE3.GPIOParameters=GPIO_PuPd,GPIO_Label,GPIO_ModeDefaultEXTI
PE3.GPIO_Label=UTS2_ECHO
PE3.GPIO_ModeDefaultEXTI=GPIO_MODE_IT_RISING_FALLING
PE3.GPIO_PuPd=GPIO_PULLUP
PE3.Signal=GPXTI3
PE4.GPIOParameters=GPIO_Label
PE4.GPIO_Label=UTS3_TRIG
PE4.Signal=GPIO_Output
PE5.GPIOParameters=GPIO_PuPd,GPIO_Label,GPIO_ModeDefaultEXTI
PE5.GPIO_Label=UTS3_ECHO
PE5.GPIO_ModeDefaultEXTI=GPIO_MODE_IT_RISING_FALLING
PE5.GPIO_PuPd=GPIO_PULLUP
PE5.Signal=GPXTI5
PE6.GPIOParameters=GPIO_Label
PE6.GPIO_Label=UTS4_TRIG
PE6.Signal=GPIO_Output
PE7.GPIOParameters=GPIO_PuPd,GPIO_Label
PE7.GPIO_Label=UTS4_ECHO
PE7.GPIO_PuPd=GPIO_PULLUP
PE7.Signal=GPIO_Input
PE8.GPIOParameters=GPIO_Label
PE8.GPIO_Label=PWM1B (TIM1_CH1N)
PE8.Mode=PWM Generation1 CH1 CH1N
PE8.Signal=TIM1_CH1N
PE9.GPIOParameters=GPIO_Label
PE9.GPIO_Label=PWM1A (TIM1_CH1)
PE9.Signal=S_TIM1_CH1
board=custom
